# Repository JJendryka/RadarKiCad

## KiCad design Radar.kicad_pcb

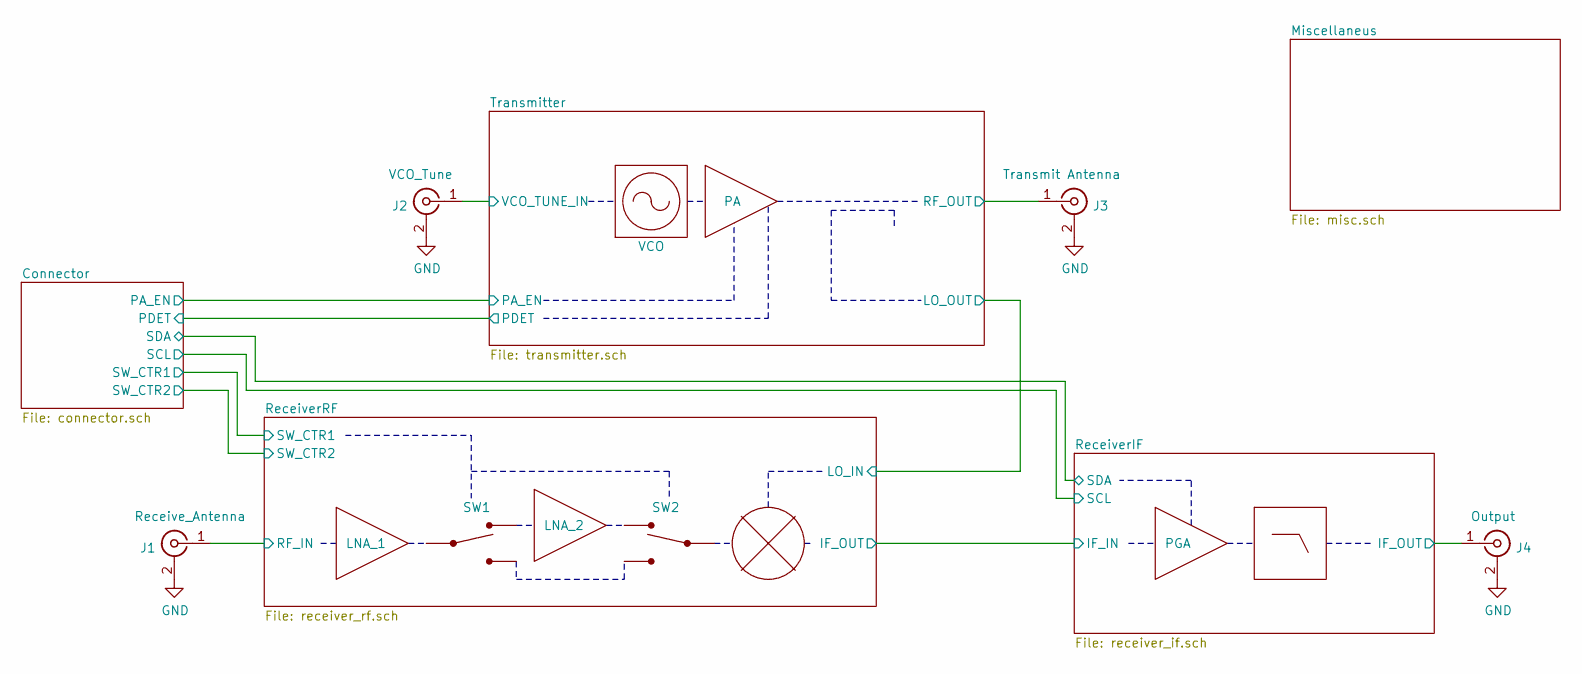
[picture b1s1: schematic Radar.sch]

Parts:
J1: Receive_Antenna; SMA_ADAM_TECH_edge
J2: VCO_Tune; SMA_ADAM_TECH_edge
J3: Transmit Antenna; SMA_ADAM_TECH_edge
J4: Output; SMA_ADAM_TECH_edge
U1: LNA_1
U2: SW1
U3: LNA_2
U4: VCO
U5: SW2
U6: PA
U7: mixer_diagram
U8: PGA
U9: lowpass_diagram

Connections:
/ReceiverIF/IF_OUT: J4.1 (In); also elsewhere on the board
/ReceiverRF/RF_IN: J1.1 (In); also elsewhere on the board
/Transmitter/RF_OUT: J3.1 (In); also elsewhere on the board
/Transmitter/VCO_TUNE_IN: J2.1 (In); also elsewhere on the board
GND: J1.2 (Ext), J2.2 (Ext), J3.2 (Ext), J4.2 (Ext); also elsewhere on the board

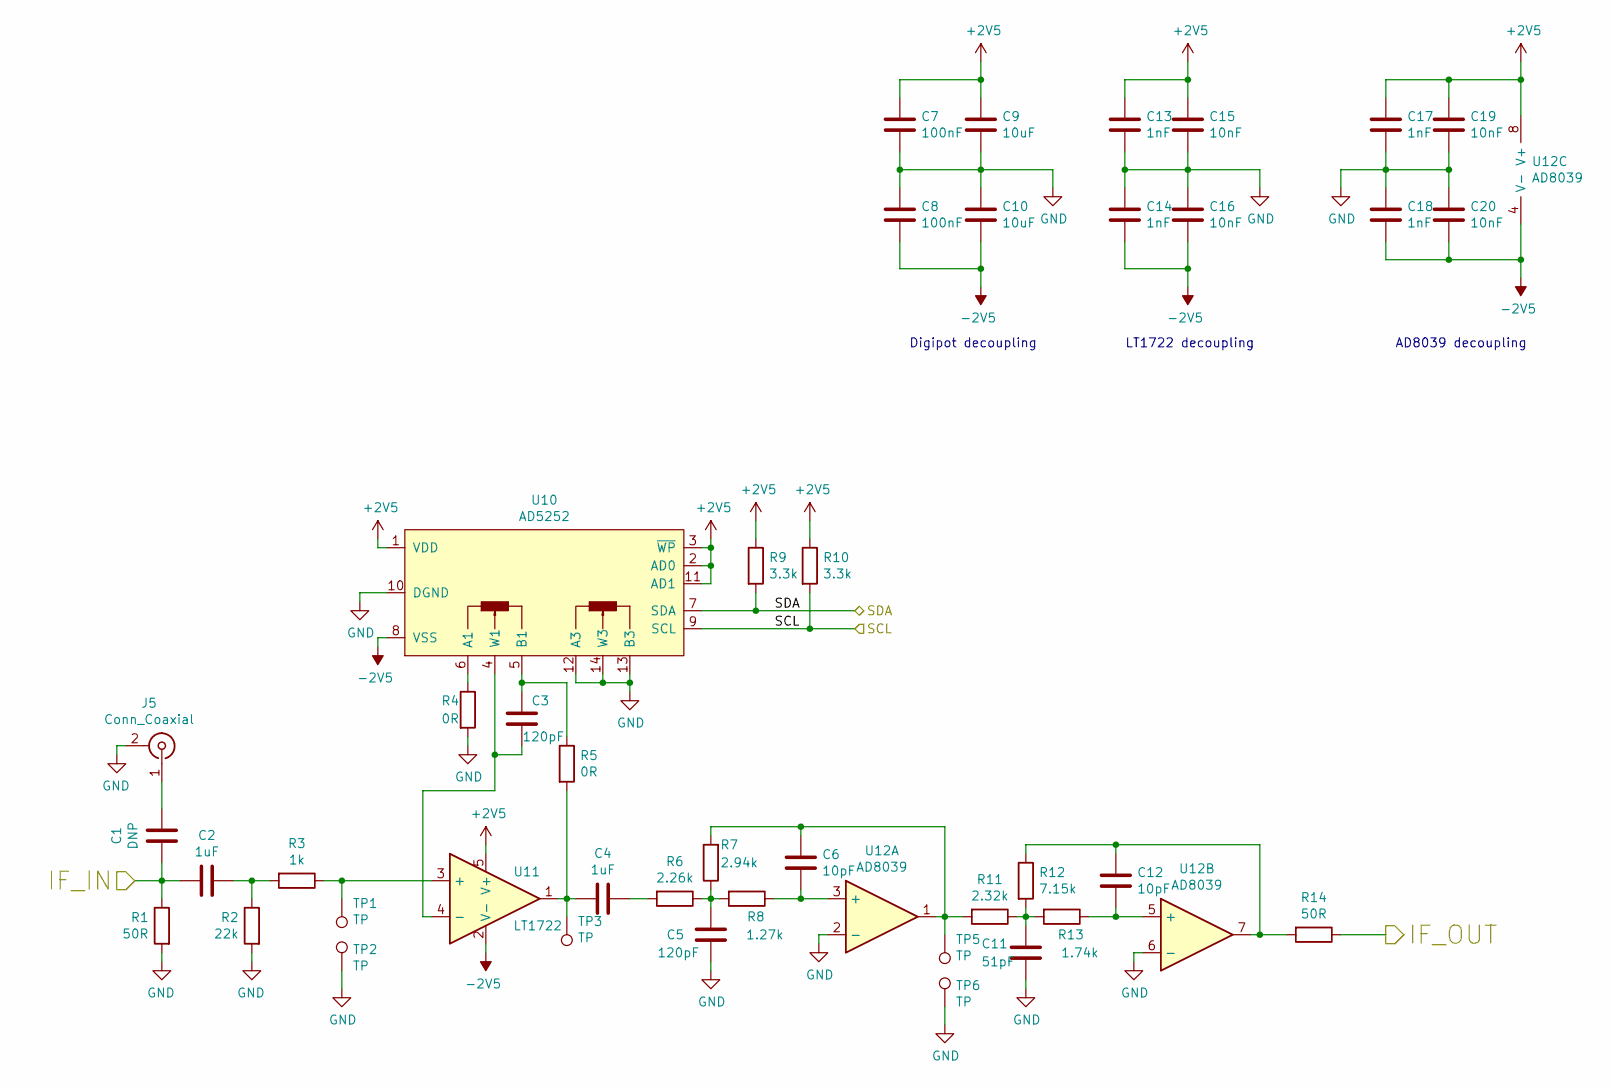
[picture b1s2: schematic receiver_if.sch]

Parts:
C1: DNP; C_0603_1608Metric_Pad1.08x0.95mm_HandSolder
C2, C4: 1uF; C_0603_1608Metric_Pad1.08x0.95mm_HandSolder
C3, C5: 120pF; C_0603_1608Metric_Pad1.08x0.95mm_HandSolder
C6, C12: 10pF; C_0603_1608Metric_Pad1.08x0.95mm_HandSolder
C7, C8: 100nF; C_0603_1608Metric_Pad1.08x0.95mm_HandSolder
C9, C10: 10uF; C_0603_1608Metric_Pad1.08x0.95mm_HandSolder
C11: 51pF; C_0603_1608Metric_Pad1.08x0.95mm_HandSolder
C13, C14, C17, C18: 1nF; C_0603_1608Metric_Pad1.08x0.95mm_HandSolder
C15, C16, C19, C20: 10nF; C_0603_1608Metric_Pad1.08x0.95mm_HandSolder
J5: Conn_Coaxial; SMA_Amphenol_132134-11_Vertical
R1, R14: 50R; R_0603_1608Metric_Pad0.98x0.95mm_HandSolder
R2: 22k; R_0603_1608Metric_Pad0.98x0.95mm_HandSolder
R3: 1k; R_0603_1608Metric_Pad0.98x0.95mm_HandSolder
R4, R5: 0R; R_0603_1608Metric_Pad0.98x0.95mm_HandSolder
R6: 2.26k; R_0603_1608Metric_Pad0.98x0.95mm_HandSolder
R7: 2.94k; R_0603_1608Metric_Pad0.98x0.95mm_HandSolder
R8: 1.27k; R_0603_1608Metric_Pad0.98x0.95mm_HandSolder
R9, R10: 3.3k; R_0603_1608Metric_Pad0.98x0.95mm_HandSolder
R11: 2.32k; R_0603_1608Metric_Pad0.98x0.95mm_HandSolder
R12: 7.15k; R_0603_1608Metric_Pad0.98x0.95mm_HandSolder
R13: 1.74k; R_0603_1608Metric_Pad0.98x0.95mm_HandSolder
TP1, TP2, TP3, TP5, TP6: TP; TestPoint_Pad_D2.0mm
U10: AD5252; TSSOP-14_4.4x5mm_P0.65mm
U11: LT1722; SOT-23-5_HandSoldering
U12: AD8039; SOIC-8_3.9x4.9mm_P1.27mm

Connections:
+2V5: C7.1, C9.1, C13.1, C15.1, C17.1, C19.1, R9.1, R10.1, U10.1 (VDD), U10.2 (AD0), U10.3 (~WP), U10.11 (AD1), U11.5 (V+), U12.8 (V+); also elsewhere on the board
-2V5: C8.2, C10.2, C14.2, C16.2, C18.2, C20.2, U10.8 (VSS), U11.2 (V-), U12.4 (V-); also elsewhere on the board
/Connector/SCL: R10.2, U10.9 (SCL); also elsewhere on the board
/Connector/SDA: R9.2, U10.7 (SDA); also elsewhere on the board
/ReceiverIF/IF_IN: C1.1, C2.1, R1.1; also elsewhere on the board
/ReceiverIF/IF_OUT: R14.1; also elsewhere on the board
GND: C5.1, C7.2, C8.1, C9.2, C10.1, C11.1, C13.2, C14.1, C15.2, C16.1, C17.2, C18.1, C19.2, C20.1, J5.2 (Ext), R1.2, R2.2, R4.2, TP2.1, TP6.1, U10.10 (DGND), U10.12 (A3), U10.13 (B3), U10.14 (W3), U12.2 (-), U12.6 (-); also elsewhere on the board
unnamed: C1.2, J5.1 (In)
unnamed: C2.2, R2.1, R3.2
unnamed: C3.1, R5.1, U10.5 (B1)
unnamed: C3.2, U10.4 (W1), U11.4 (-)
unnamed: C4.1, R6.2
unnamed: C4.2, R5.2, TP3.1, U11.1
unnamed: C5.2, R6.1, R7.1, R8.2
unnamed: C6.1, R7.2, R11.2, TP5.1, U12.1
unnamed: C6.2, R8.1, U12.3 (+)
unnamed: C11.2, R11.1, R12.2, R13.2
unnamed: C12.1, R12.1, R14.2, U12.7
unnamed: C12.2, R13.1, U12.5 (+)
unnamed: R3.1, TP1.1, U11.3 (+)
unnamed: R4.1, U10.6 (A1)

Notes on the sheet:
Digipot decoupling
LT1722 decoupling
AD8039 decoupling

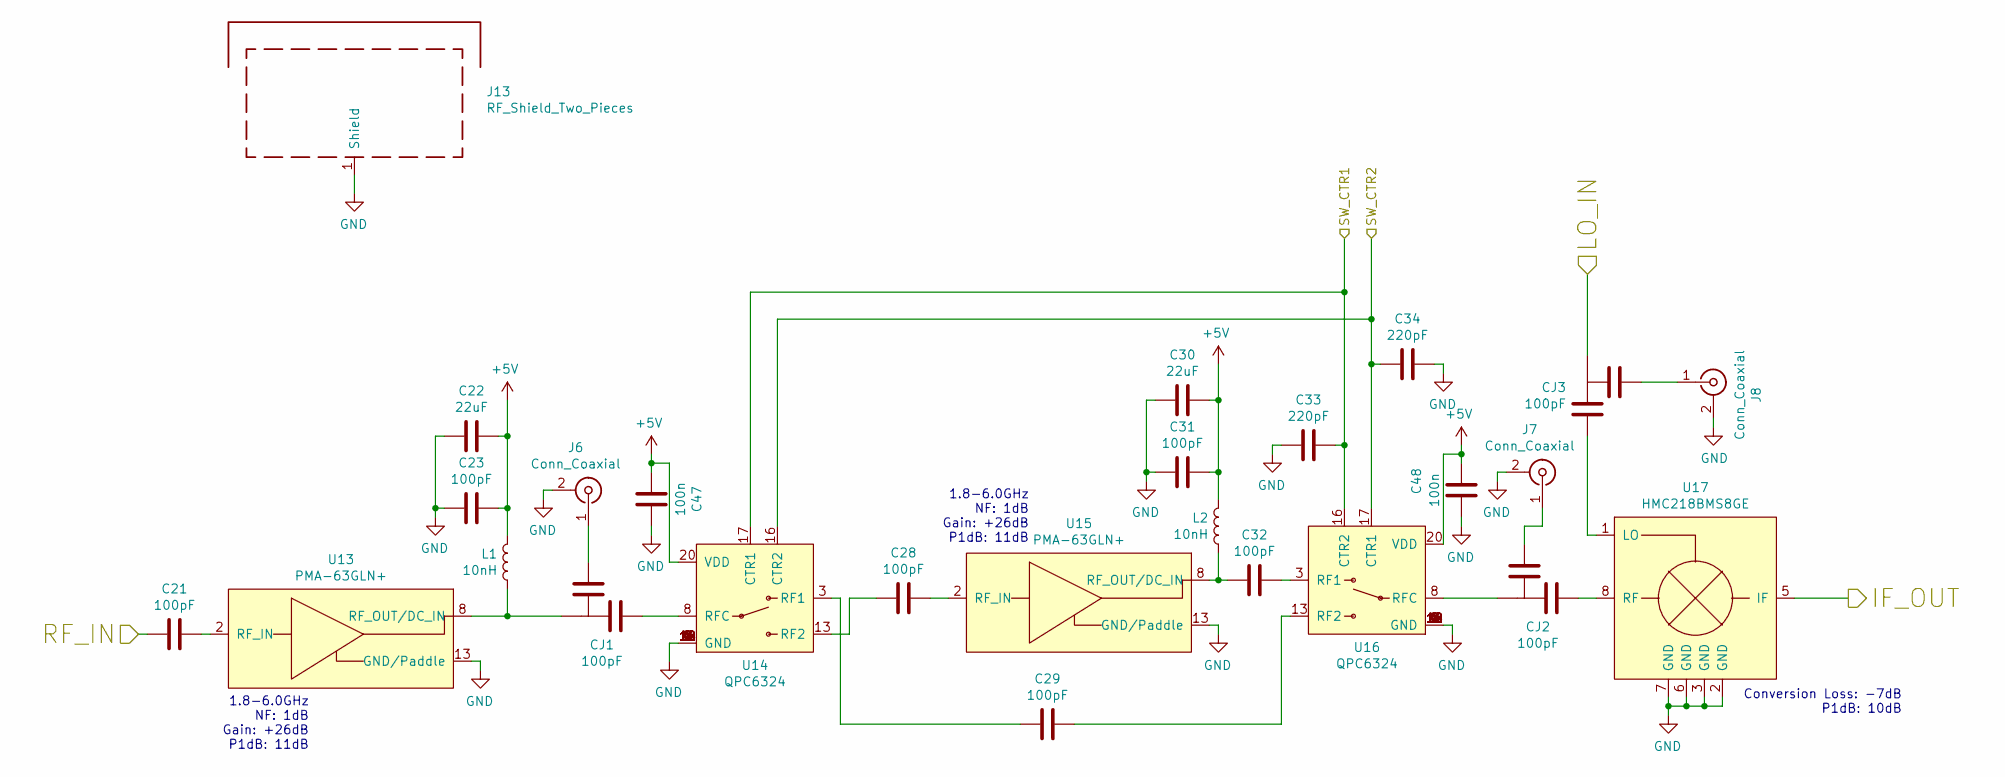
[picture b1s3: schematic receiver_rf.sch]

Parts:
C21, C28, C29, C32: 100pF; 0402_Tapered
C22, C30: 22uF; C_0603_1608Metric_Pad1.08x0.95mm_HandSolder
C23, C31: 100pF; C_0603_1608Metric_Pad1.08x0.95mm_HandSolder
C33, C34: 220pF; C_0603_1608Metric_Pad1.08x0.95mm_HandSolder
C47, C48: 100n; C_0603_1608Metric_Pad1.08x0.95mm_HandSolder
CJ1, CJ2, CJ3: 100pF; 0402_Jumper_Tapered
J6, J7, J8: Conn_Coaxial; SMA_Amphenol_132134-11_Vertical
J13: RF_Shield_Two_Pieces; Laird_Technologies_BMI-S-209-F_29.36x18.50mm
L1, L2: 10nH; L_0402_1005Metric
U13, U15: PMA-63GLN+; QFN-12-1EP_3x3mm_P0.51mm_EP1.45x1.45mm
U14, U16: QPC6324; QFN-20-1EP_4x4mm_P0.5mm_EP2.5x2.5mm
U17: HMC218BMS8GE; MSOP-8-1EP_3x3mm_P0.65mm_EP1.73x1.85mm

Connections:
+5V: C22.2, C23.2, C30.2, C31.2, C47.1, C48.1, L1.1, L2.1, U14.20 (VDD), U16.20 (VDD); also elsewhere on the board
/Connector/SW_CTR1: C33.2, U14.17 (CTR1), U16.16 (CTR2); also elsewhere on the board
/Connector/SW_CTR2: C34.1, U14.16 (CTR2), U16.17 (CTR1); also elsewhere on the board
/ReceiverIF/IF_IN: U17.5 (IF); also elsewhere on the board
/ReceiverRF/LO_IN: CJ3.1; also elsewhere on the board
/ReceiverRF/RF_IN: C21.1; also elsewhere on the board
GND: C22.1, C23.1, C30.1, C31.1, C33.1, C34.2, C47.2, C48.2, J6.2 (Ext), J7.2 (Ext), J8.2 (Ext), J13.1, U13.13 (GND/Paddle), U14.1 (GND), U14.2 (GND), U14.4 (GND), U14.5 (GND), U14.6 (GND), U14.7 (GND), U14.9 (GND), U14.10 (GND), U14.11 (GND), U14.12 (GND), U14.14 (GND), U14.15 (GND), U14.18 (GND), U14.19 (GND), U15.13 (GND/Paddle), U16.1 (GND), U16.2 (GND), U16.4 (GND), U16.5 (GND), U16.6 (GND), U16.7 (GND), U16.9 (GND), U16.10 (GND), U16.11 (GND), U16.12 (GND), U16.14 (GND), U16.15 (GND), U16.18 (GND), U16.19 (GND), U17.2 (GND), U17.3 (GND), U17.6 (GND), U17.7 (GND); also elsewhere on the board
unnamed: C21.2, U13.2 (RF_IN)
unnamed: C28.1, U14.13 (RF2)
unnamed: C28.2, U15.2 (RF_IN)
unnamed: C29.1, U14.3 (RF1)
unnamed: C29.2, U16.13 (RF2)
unnamed: C32.1, L2.2, U15.8 (RF_OUT/DC_IN)
unnamed: C32.2, U16.3 (RF1)
unnamed: CJ1.1, L1.2, U13.8 (RF_OUT/DC_IN)
unnamed: CJ1.2, U14.8 (RFC)
unnamed: CJ1.3, J6.1 (In)
unnamed: CJ2.1, U16.8 (RFC)
unnamed: CJ2.2, U17.8 (RF)
unnamed: CJ2.3, J7.1 (In)
unnamed: CJ3.2, U17.1 (LO)
unnamed: CJ3.3, J8.1 (In)

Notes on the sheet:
1.8-6.0GHz NF: 1dB Gain: +26dB P1dB: 11dB
Conversion Loss: -7dB P1dB: 10dB

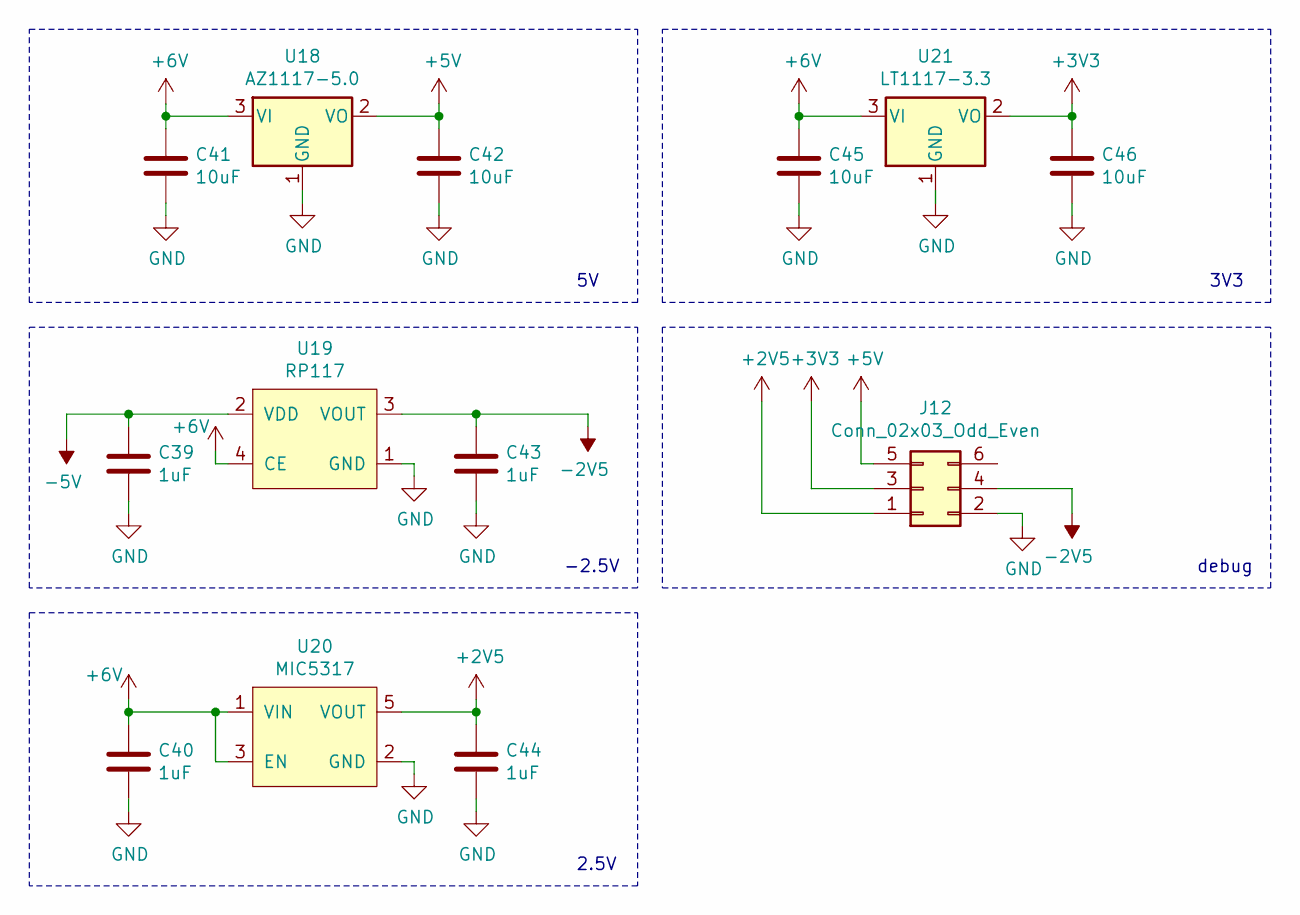
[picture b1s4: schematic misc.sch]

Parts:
C39, C40, C43, C44: 1uF; C_0603_1608Metric_Pad1.08x0.95mm_HandSolder
C41, C42, C45, C46: 10uF; C_0603_1608Metric_Pad1.08x0.95mm_HandSolder
J12: Conn_02x03_Odd_Even; PinHeader_2x03_P2.54mm_Vertical
U18: AZ1117-5.0; SOT-223-3_TabPin2
U19: RP117; SOT-353_SC-70-5_Handsoldering
U20: MIC5317; SOT-23-5_HandSoldering
U21: LT1117-3.3; SOT-223-3_TabPin2

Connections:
+2V5: C44.1, J12.1, U20.5 (VOUT); also elsewhere on the board
+3V3: C46.1, J12.3, U21.2 (VO); also elsewhere on the board
+5V: C42.1, J12.5, U18.2 (VO); also elsewhere on the board
+6V: C40.1, C41.1, C45.1, U18.3 (VI), U19.4 (CE), U20.1 (VIN), U20.3 (EN), U21.3 (VI); also elsewhere on the board
-2V5: C43.1, J12.4, U19.3 (VOUT); also elsewhere on the board
-5V: C39.1, U19.2 (VDD); also elsewhere on the board
GND: C39.2, C40.2, C41.2, C42.2, C43.2, C44.2, C45.2, C46.2, J12.2, U18.1 (GND), U19.1 (GND), U20.2 (GND), U21.1 (GND); also elsewhere on the board

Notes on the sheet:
-2.5V
2.5V
3V3
debug

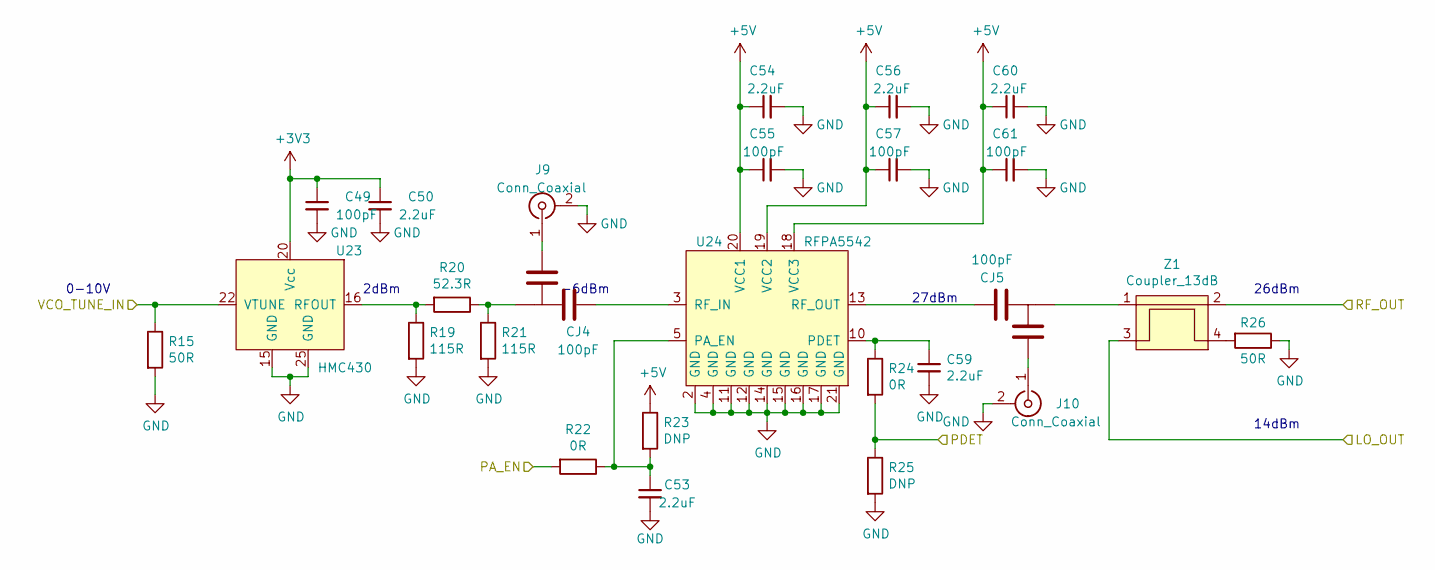
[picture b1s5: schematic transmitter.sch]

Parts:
C49: 100pF; C_0603_1608Metric_Pad1.08x0.95mm_HandSolder
C50, C53, C54, C56, C59, C60: 2.2uF; C_0603_1608Metric_Pad1.08x0.95mm_HandSolder
C55, C57, C61: 100pF; R_0402_1005Metric_Pad0.72x0.64mm_HandSolder
CJ4, CJ5: 100pF; 0402_Jumper_Tapered
J9, J10: Conn_Coaxial; SMA_Amphenol_132134-11_Vertical
R15: 50R; R_0603_1608Metric_Pad0.98x0.95mm_HandSolder
R19, R21: 115R; R_0402_1005Metric
R20: 52.3R; R_0402_1005Metric
R22, R24: 0R; R_0603_1608Metric_Pad0.98x0.95mm_HandSolder
R23, R25: DNP; R_0603_1608Metric_Pad0.98x0.95mm_HandSolder
R26: 50R; 0402_Tapered
U23: HMC430; QFN-24-1EP_4x4mm_P0.5mm_EP2.6x2.6mm
U24: RFPA5542; QFN-20-1EP_4x4mm_P0.5mm_EP2.5x2.5mm
Z1: Coupler_13dB

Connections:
+3V3: C49.1, C50.1, U23.20 (Vcc); also elsewhere on the board
+5V: C54.1, C55.1, C56.1, C57.1, C60.1, C61.1, R23.1, U24.18 (VCC3), U24.19 (VCC2), U24.20 (VCC1); also elsewhere on the board
/Connector/PA_EN: R22.2; also elsewhere on the board
/Connector/PDET: R24.2, R25.1; also elsewhere on the board
/ReceiverRF/LO_IN: Z1.3; also elsewhere on the board
/Transmitter/RF_OUT: Z1.2; also elsewhere on the board
/Transmitter/VCO_TUNE_IN: R15.1, U23.22 (VTUNE); also elsewhere on the board
GND: C49.2, C50.2, C53.2, C54.2, C55.2, C56.2, C57.2, C59.2, C60.2, C61.2, J9.2 (Ext), J10.2 (Ext), R15.2, R19.2, R21.2, R25.2, R26.1, U23.15 (GND), U23.25 (GND), U24.2 (GND), U24.4 (GND), U24.11 (GND), U24.12 (GND), U24.14 (GND), U24.15 (GND), U24.16 (GND), U24.17 (GND), U24.21 (GND); also elsewhere on the board
unnamed: C53.1, R22.1, R23.2, U24.5 (PA_EN)
unnamed: C59.1, R24.1, U24.10 (PDET)
unnamed: CJ4.1, R20.1, R21.1
unnamed: CJ4.2, U24.3 (RF_IN)
unnamed: CJ4.3, J9.1 (In)
unnamed: CJ5.1, Z1.1
unnamed: CJ5.2, U24.13 (RF_OUT)
unnamed: CJ5.3, J10.1 (In)
unnamed: R19.1, R20.2, U23.16 (RFOUT)
unnamed: R26.2, Z1.4

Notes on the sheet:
27dBm
26dBm
14dBm
-6dBm
2dBm
0-10V

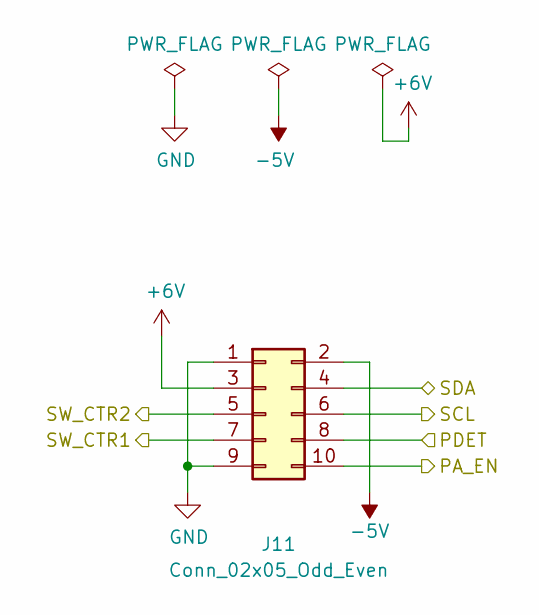
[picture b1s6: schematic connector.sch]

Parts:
J11: Conn_02x05_Odd_Even; IDC-Header_2x05_P2.54mm_Vertical

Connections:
+6V: J11.3; also elsewhere on the board
-5V: J11.2; also elsewhere on the board
/Connector/PA_EN: J11.10; also elsewhere on the board
/Connector/PDET: J11.8; also elsewhere on the board
/Connector/SCL: J11.6; also elsewhere on the board
/Connector/SDA: J11.4; also elsewhere on the board
/Connector/SW_CTR1: J11.7; also elsewhere on the board
/Connector/SW_CTR2: J11.5; also elsewhere on the board
GND: J11.1, J11.9; also elsewhere on the board

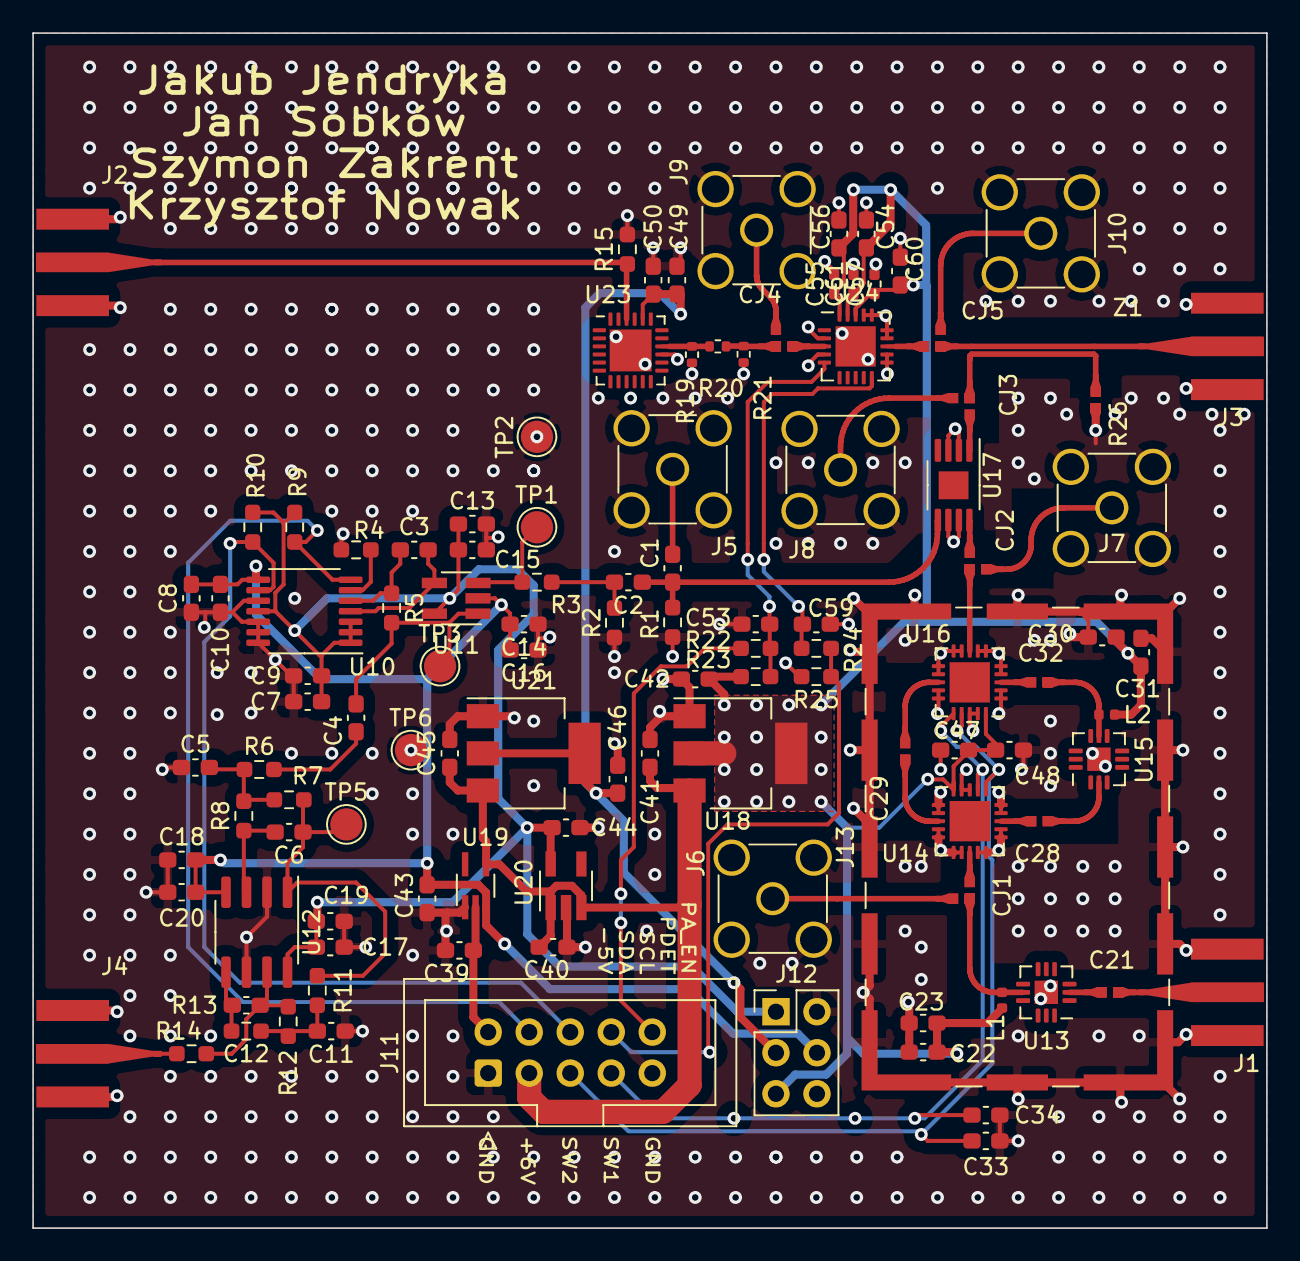
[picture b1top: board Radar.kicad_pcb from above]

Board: 4 copper layers, 76.4 x 74.0 mm, 113 parts (0 on the bottom side), 58 nets.

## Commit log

2020-10-15 Block diagram added
2020-10-15 Added mixer and LNA
2020-10-21 fixed library
2020-11-03 Architecture of IF
2020-11-11 Added transmitter
2021-03-17 Finished IF
2021-03-25 Merged transmitter
2021-03-25 Added opamp and footprints
2021-03-25 Fixed sheets and changed footprints and capacitor values
2021-03-26 Schematic finishing touches
2021-03-31 Added connector
2021-04-01 -2.5V regulator footprint added. RF switch footprint created and added.
2021-04-01 First layout
2021-04-02 Shrunk the microwave section
2021-04-02 Curved tracks
2021-04-02 Fixed connector
2021-04-02 Moved test points
2021-04-05 IF and power layout mostly finished
2021-04-06 Added RX shield
2021-04-06 Finished TX layout
2021-04-06 Removed soldermask from RF paths
2021-04-06 replaced 78xx series 3V3 regulator for 1117 series
2021-04-18 Added names
2021-04-26 Added via stitching
2021-04-28 Added pinout
2021-04-28 Generated gerbers
2021-08-18 Added interactive bom
2022-04-13 Added pdfs
